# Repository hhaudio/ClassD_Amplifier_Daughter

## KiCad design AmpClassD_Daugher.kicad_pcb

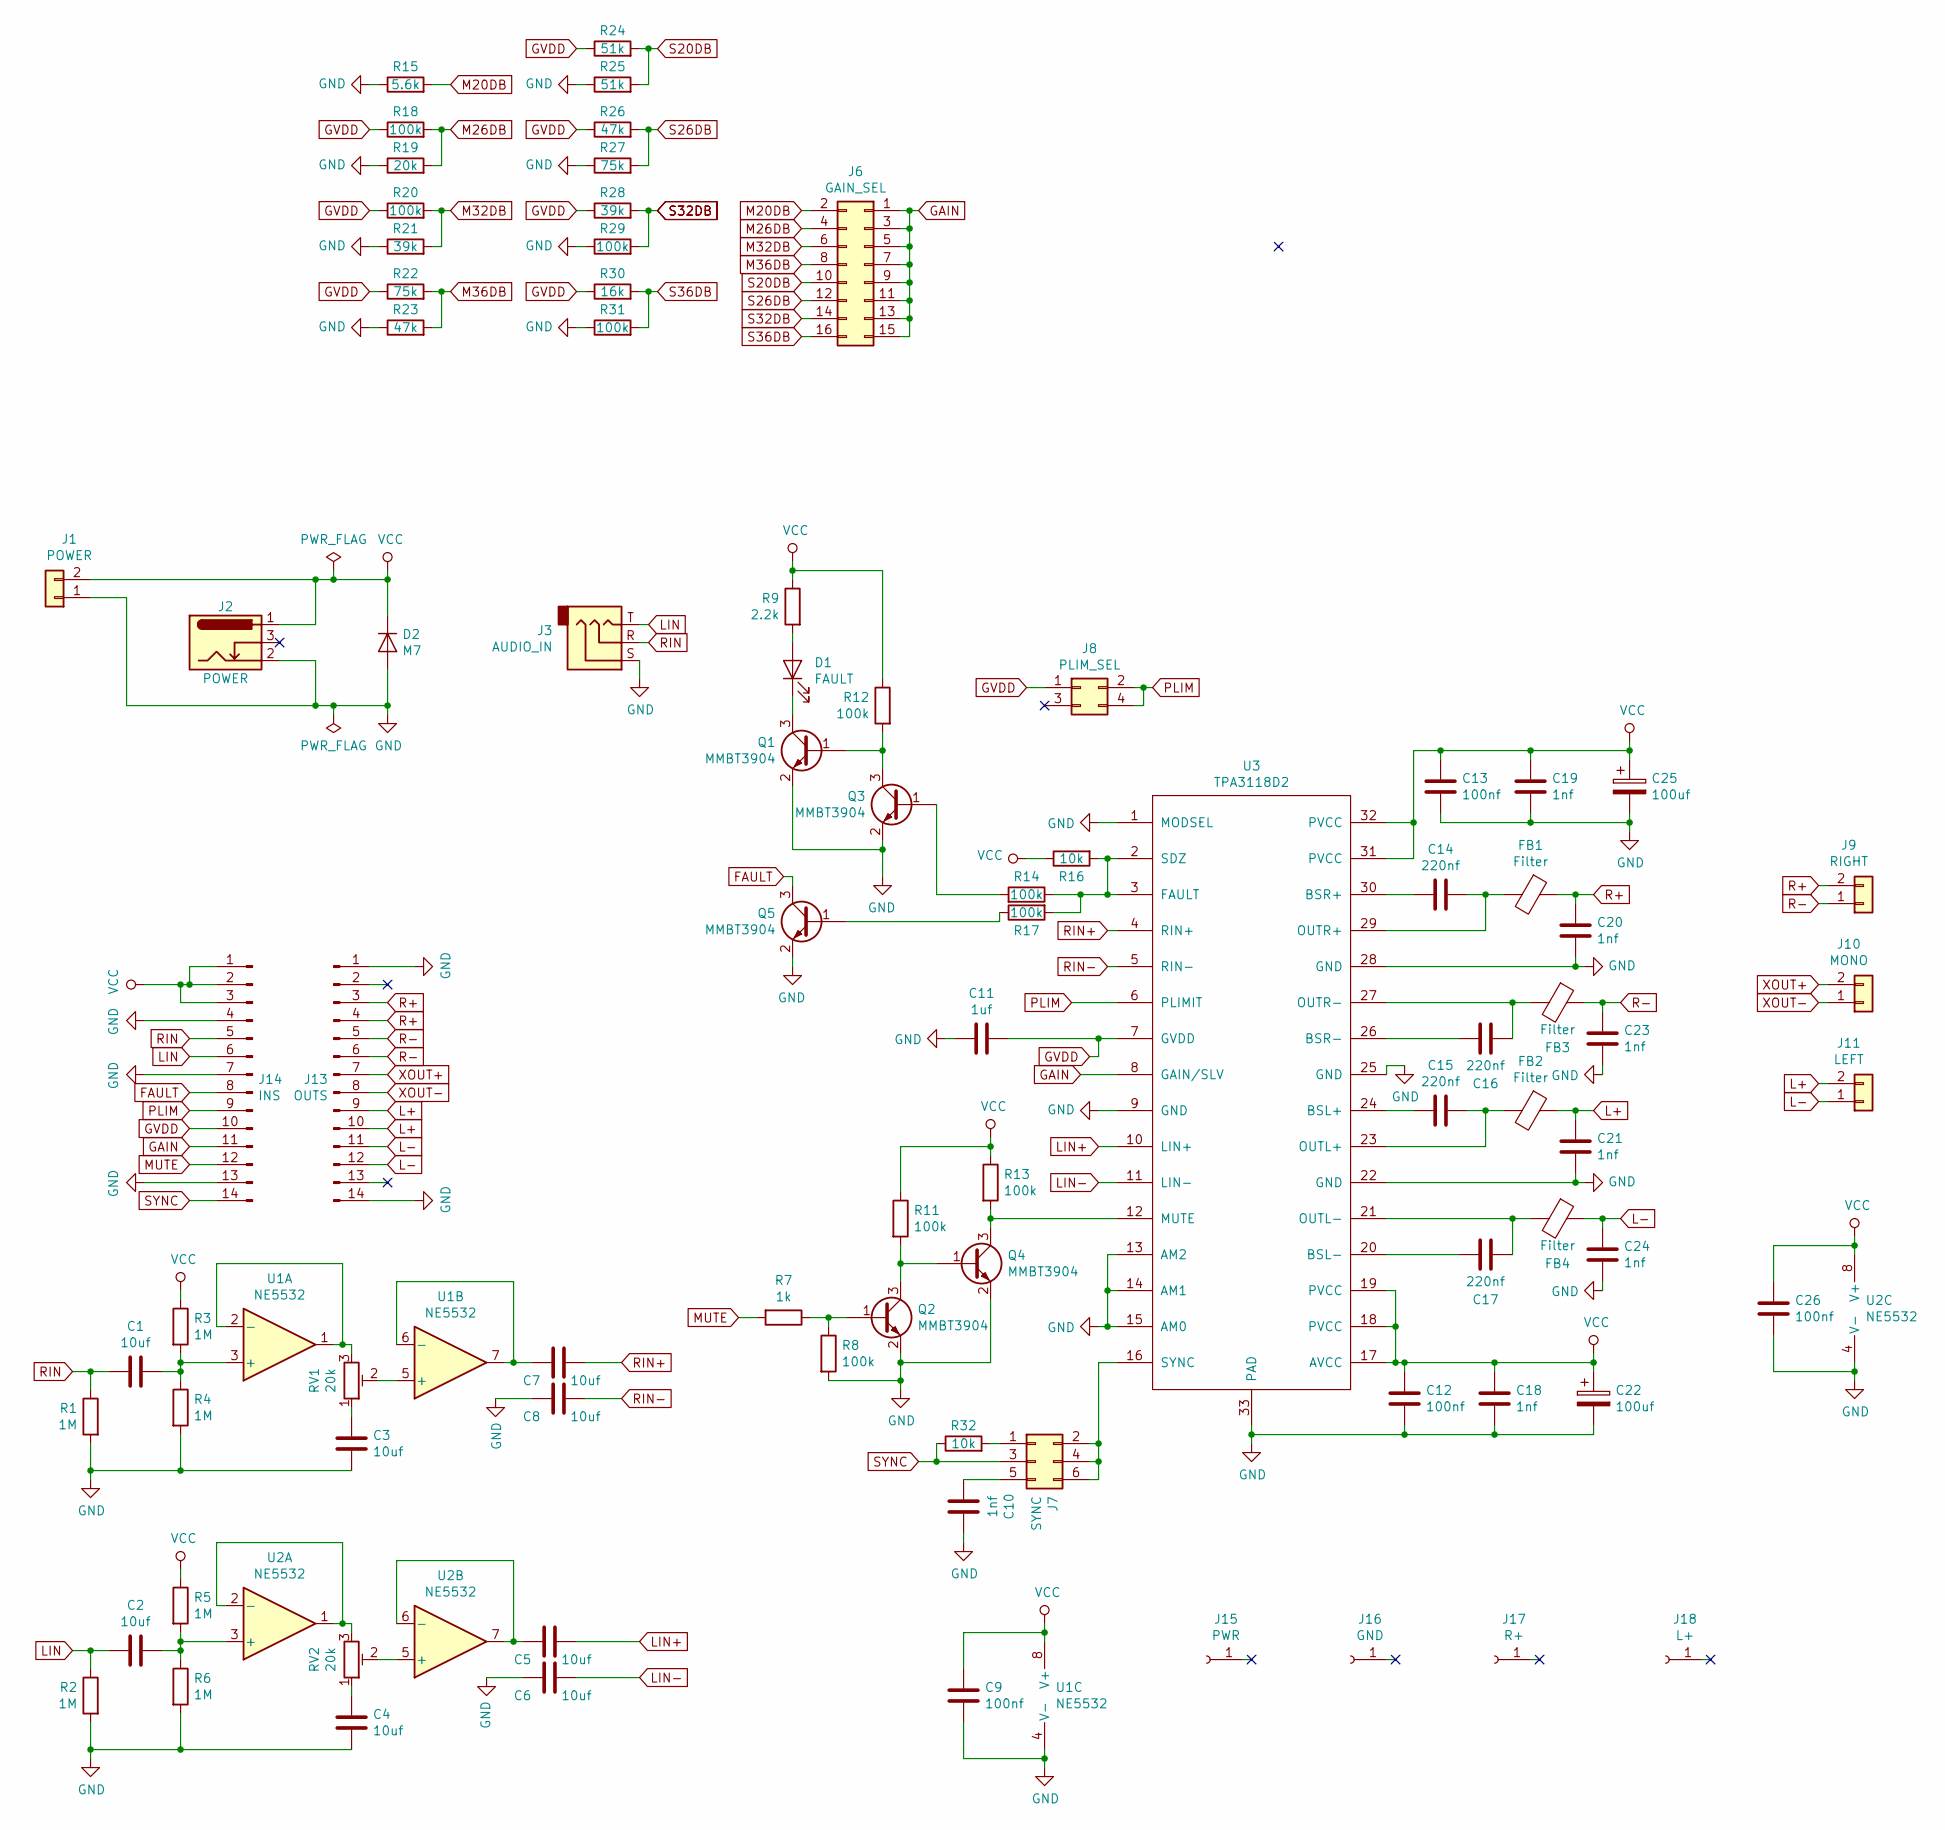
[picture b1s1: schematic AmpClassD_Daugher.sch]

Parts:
C1, C2, C3, C4, C5, C6, C7, C8: 10uf; C_0603_1608Metric_Pad1.05x0.95mm_HandSolder_SmallRef; LCSC C440198
C9, C12, C13, C26: 100nf; C_0603_1608Metric_Pad1.05x0.95mm_HandSolder_SmallRef; LCSC C14663
C10, C18, C19, C20, C21, C23, C24: 1nf; C_0603_1608Metric_Pad1.05x0.95mm_HandSolder_SmallRef; LCSC C1588
C11: 1uf; C_0603_1608Metric_Pad1.05x0.95mm_HandSolder_SmallRef; LCSC C15849
C14, C15, C16, C17: 220nf; C_0603_1608Metric_Pad1.05x0.95mm_HandSolder_SmallRef; LCSC C21120
C22, C25: 100uf; CP_Elec_6.3x7.7; LCSC C311622
D1: FAULT; LED_0805_2012Metric_Pad1.15x1.40mm_HandSolder; LCSC C84256
D2: M7; D_SMA; LCSC C95872
FB1, FB2, FB3, FB4: Filter; L_1206_3216Metric_Pad1.42x1.75mm_HandSolder; LCSC C124704
J1: POWER; Phoenix_Stacked_Marking2_Wider_NoRef_Centered
J2: POWER; SMD_DC_Barrel_JLC; LCSC C397342
J3: AUDIO_IN; 3.5mm_JLC_PJ-321A-4A_TRS_Silk; LCSC C879743
J6: GAIN_SEL; PinHeader_2x08_P2.54mm_Vertical_SMD; LCSC C2884017
J7: SYNC; PinHeader_2x03_P2.54mm_Vertical_SMD; LCSC C780054
J8: PLIM_SEL; PinHeader_2x02_P2.54mm_Vertical_SMD; LCSC C3294460
J9: RIGHT; Phoenix_Stacked_Marking2_Wider_NoRef_Centered
J10: MONO; Phoenix_Stacked_Marking2_Wider_NoRef_Centered
J11: LEFT; Phoenix_Stacked_Marking2_Wider_NoRef_Centered
J13: OUTS; PinHeader_1x14_P2.54mm_Vertical
J14: INS; PinHeader_1x14_P2.54mm_Vertical
J15: PWR; M3_Plated
J16: GND; M3_Plated
J17: R+; M3_Plated
J18: L+; M3_Plated
Q1, Q2, Q3, Q4, Q5: MMBT3904; SOT-23; LCSC C20526
R1, R2, R3, R4, R5, R6: 1M; R_0603_1608Metric_Pad1.05x0.95mm_HandSolder_SmallRef; LCSC C22935
R7: 1k; R_0603_1608Metric_Pad1.05x0.95mm_HandSolder_SmallRef; LCSC C21190
R8, R11, R12, R13, R14, R17, R18, R20, R29, R31: 100k; R_0603_1608Metric_Pad1.05x0.95mm_HandSolder_SmallRef; LCSC C25803
R9: 2.2k; R_0603_1608Metric_Pad1.05x0.95mm_HandSolder_SmallRef; LCSC C4190
R15: 5.6k; R_0603_1608Metric_Pad1.05x0.95mm_HandSolder_SmallRef; LCSC C23189
R16, R32: 10k; R_0603_1608Metric_Pad1.05x0.95mm_HandSolder_SmallRef; LCSC C25804
R19: 20k; R_0603_1608Metric_Pad1.05x0.95mm_HandSolder_SmallRef; LCSC C4184
R21, R28: 39k; R_0603_1608Metric_Pad1.05x0.95mm_HandSolder_SmallRef; LCSC C23153
R22, R27: 75k; R_0603_1608Metric_Pad1.05x0.95mm_HandSolder_SmallRef; LCSC C23242
R23, R26: 47k; R_0603_1608Metric_Pad1.05x0.95mm_HandSolder_SmallRef; LCSC C23162
R24, R25: 51k; R_0603_1608Metric_Pad1.05x0.95mm_HandSolder_SmallRef; LCSC C23196
R30: 16k; R_0603_1608Metric_Pad1.05x0.95mm_HandSolder_SmallRef; LCSC C22818
RV1, RV2: 20k; SMD_TRIM_JLC; LCSC C128550
U1, U2: NE5532; SO-8_3.9x4.9mm_P1.27mm; LCSC C7426
U3: TPA3118D2; HTSSOP-32-1EP_6.1x11mm_P0.65mm_EP5.2x11mm_Mask4.11x4.36mm_T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; LCSC C46497

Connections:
FAULT: J14.8, Q5.3 (C)
GAIN: J6.1, J6.3, J6.5, J6.7, J6.9, J6.11, J6.13, J6.15, J14.11, U3.8 (GAIN/SLV)
GND: C3.2, C4.2, C6.2, C8.2, C9.2, C10.1, C11.2, C12.2, C13.2, C18.2, C19.2, C20.2, C21.2, C22.2, C23.2, C24.2, C25.2, C26.2, D2.2 (A), J1.1, J2.2, J3.S, J13.1, J13.14, J14.4, J14.7, J14.13, Q1.2 (E), Q2.2 (E), Q3.2 (E), Q4.2 (E), Q5.2 (E), R1.2, R2.2, R4.2, R6.2, R8.2, R15.1, R19.1, R21.1, R23.1, R25.1, R27.1, R29.1, R31.1, U1.4 (V-), U2.4 (V-), U3.1 (MODSEL), U3.9 (GND), U3.13 (AM2), U3.14 (AM1), U3.15 (AM0), U3.22 (GND), U3.25 (GND), U3.28 (GND), U3.33 (PAD)
GVDD: C11.1, J8.1, J14.10, R18.1, R20.1, R22.1, R24.1, R26.1, R28.1, R30.1, U3.7 (GVDD)
L+: C21.1, FB2.1, J11.2, J13.9, J13.10
L-: C24.1, FB4.1, J11.1, J13.11, J13.12
LIN: C2.2, J3.T, J14.6, R2.1
LIN+: C5.1, U3.10 (LIN+)
LIN-: C6.1, U3.11 (LIN-)
M20DB: J6.2, R15.2
M26DB: J6.4, R18.2, R19.2
M32DB: J6.6, R20.2, R21.2
M36DB: J6.8, R22.2, R23.2
MUTE: J14.12, R7.2
unnamed: C1.1, R3.2, R4.1, U1.3 (+)
unnamed: C2.1, R5.2, R6.1, U2.3 (+)
unnamed: C3.1, RV1.1
unnamed: C4.1, RV2.1
unnamed: C5.2, U2.6 (-), U2.7
unnamed: C7.2, U1.6 (-), U1.7
unnamed: C10.2, J7.5
unnamed: C14.1, FB1.2, U3.29 (OUTR+)
unnamed: C14.2, U3.30 (BSR+)
unnamed: C15.1, FB2.2, U3.23 (OUTL+)
unnamed: C15.2, U3.24 (BSL+)
unnamed: C16.1, U3.26 (BSR-)
unnamed: C16.2, FB3.2, U3.27 (OUTR-)
unnamed: C17.1, U3.20 (BSL-)
unnamed: C17.2, FB4.2, U3.21 (OUTL-)
unnamed: D1.1 (K), Q1.3 (C)
unnamed: D1.2 (A), R9.2
unnamed: J7.1, R32.2
unnamed: J7.2, J7.4, J7.6, U3.16 (SYNC)
unnamed: Q1.1 (B), Q3.3 (C), R12.2
unnamed: Q2.1 (B), R7.1, R8.1
unnamed: Q2.3 (C), Q4.1 (B), R11.2
unnamed: Q3.1 (B), R14.2
unnamed: Q4.3 (C), R13.2, U3.12 (MUTE)
unnamed: Q5.1 (B), R17.1
unnamed: R14.1, R16.2, R17.2, U3.2 (SDZ), U3.3 (FAULT)
unnamed: RV1.2, U1.5 (+)
unnamed: RV1.3, U1.1, U1.2 (-)
unnamed: RV2.2, U2.5 (+)
unnamed: RV2.3, U2.1, U2.2 (-)
PLIM: J8.2, J8.4, J14.9, U3.6 (PLIMIT)
R+: C20.1, FB1.1, J9.2, J13.3, J13.4
R-: C23.1, FB3.1, J9.1, J13.5, J13.6
RIN: C1.2, J3.R, J14.5, R1.1
RIN+: C7.1, U3.4 (RIN+)
RIN-: C8.1, U3.5 (RIN-)
S20DB: J6.10, R24.2, R25.2
S26DB: J6.12, R26.2, R27.2
S32DB: J6.14, R28.2, R29.2
S36DB: J6.16, R30.2, R31.2
SYNC: J7.3, J14.14, R32.1
VCC: C9.1, C12.1, C13.1, C18.1, C19.1, C22.1, C25.1, C26.1, D2.1 (K), J1.2, J2.1, J14.1, J14.2, J14.3, R3.1, R5.1, R9.1, R11.1, R12.1, R13.1, R16.1, U1.8 (V+), U2.8 (V+), U3.17 (AVCC), U3.18 (PVCC), U3.19 (PVCC), U3.31 (PVCC), U3.32 (PVCC)
XOUT+: J10.2, J13.7
XOUT-: J10.1, J13.8

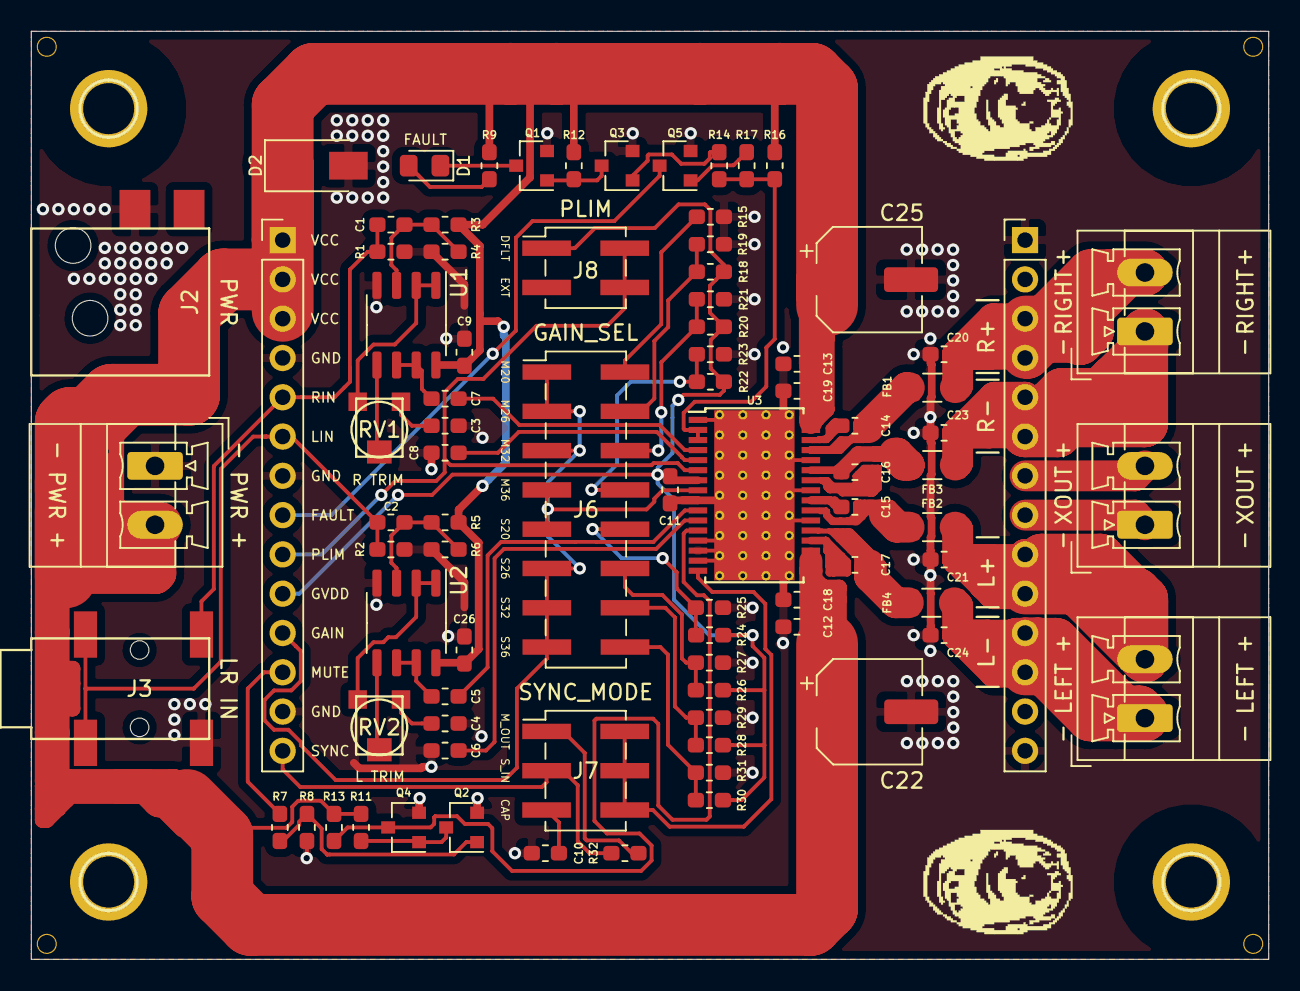
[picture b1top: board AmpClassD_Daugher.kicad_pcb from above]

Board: 2 copper layers, 80.0 x 60.0 mm, 88 parts (0 on the bottom side), 58 nets.

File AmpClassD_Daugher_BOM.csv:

Comment,Designator,Footprint,LCSC
"1uf","C11","Capacitor_SMD:C_0603_1608Metric_Pad1.05x0.95mm_HandSolder_SmallRef","C15849"
"100nf","C9,C12,C13,C26","Capacitor_SMD:C_0603_1608Metric_Pad1.05x0.95mm_HandSolder_SmallRef","C14663"
"220nf","C14,C15,C16,C17","Capacitor_SMD:C_0603_1608Metric_Pad1.05x0.95mm_HandSolder_SmallRef","C21120"
"1nf","C10,C18,C19,C20,C21,C23,C24","Capacitor_SMD:C_0603_1608Metric_Pad1.05x0.95mm_HandSolder_SmallRef","C1588"
"100uf","C22,C25","Capacitor_SMD:CP_Elec_6.3x7.7","C311622"
"10uf","C1,C2,C3,C4,C5,C6,C7,C8","Capacitor_SMD:C_0603_1608Metric_Pad1.05x0.95mm_HandSolder_SmallRef","C440198"
"FAULT","D1","LED_SMD:LED_0805_2012Metric_Pad1.15x1.40mm_HandSolder","C84256"
"M7","D2","Diode_SMD:D_SMA","C95872"
"Filter","FB1,FB2,FB3,FB4","Inductor_SMD:L_1206_3216Metric_Pad1.42x1.75mm_HandSolder","C124704"
"POWER","J1","HammerheadAudio:Phoenix_Stacked_Marking2_Wider_NoRef_Centered",""
"MONO","J10","HammerheadAudio:Phoenix_Stacked_Marking2_Wider_NoRef_Centered",""
"LEFT","J11","HammerheadAudio:Phoenix_Stacked_Marking2_Wider_NoRef_Centered",""
"OUTS","J13","Connector_PinHeader_2.54mm:PinHeader_1x14_P2.54mm_Vertical",""
"INS","J14","Connector_PinHeader_2.54mm:PinHeader_1x14_P2.54mm_Vertical",""
"PWR","J15","HammerheadAudio:M3_Plated",""
"GND","J16","HammerheadAudio:M3_Plated",""
"R+","J17","HammerheadAudio:M3_Plated",""
"L+","J18","HammerheadAudio:M3_Plated",""
"POWER","J2","Crossley_Footprints:SMD_DC_Barrel_JLC","C397342"
"AUDIO_IN","J3","HammerheadAudio:3.5mm_JLC_PJ-321A-4A_TRS_Silk","C879743"
"GAIN_SEL","J6","Connector_PinHeader_2.54mm:PinHeader_2x08_P2.54mm_Vertical_SMD","C2884017"
"SYNC","J7","Connector_PinHeader_2.54mm:PinHeader_2x03_P2.54mm_Vertical_SMD","C780054"
"PLIM_SEL","J8","Connector_PinHeader_2.54mm:PinHeader_2x02_P2.54mm_Vertical_SMD","C3294460"
"RIGHT","J9","HammerheadAudio:Phoenix_Stacked_Marking2_Wider_NoRef_Centered",""
"MMBT3904","Q1,Q2,Q3,Q4,Q5","Package_TO_SOT_SMD:SOT-23","C20526"
"100k","R8,R11,R12,R13,R14,R17,R18,R20,R29,R31","Resistor_SMD:R_0603_1608Metric_Pad1.05x0.95mm_HandSolder_SmallRef","C25803"
"5.6k","R15","Resistor_SMD:R_0603_1608Metric_Pad1.05x0.95mm_HandSolder_SmallRef","C23189"
"10k","R16,R32","Resistor_SMD:R_0603_1608Metric_Pad1.05x0.95mm_HandSolder_SmallRef","C25804"
"20k","R19","Resistor_SMD:R_0603_1608Metric_Pad1.05x0.95mm_HandSolder_SmallRef","C4184"
"39k","R21,R28","Resistor_SMD:R_0603_1608Metric_Pad1.05x0.95mm_HandSolder_SmallRef","C23153"
"75k","R22,R27","Resistor_SMD:R_0603_1608Metric_Pad1.05x0.95mm_HandSolder_SmallRef","C23242"
"47k","R23,R26","Resistor_SMD:R_0603_1608Metric_Pad1.05x0.95mm_HandSolder_SmallRef","C23162"
"51k","R24,R25","Resistor_SMD:R_0603_1608Metric_Pad1.05x0.95mm_HandSolder_SmallRef","C23196"
"1M","R1,R2,R3,R4,R5,R6","Resistor_SMD:R_0603_1608Metric_Pad1.05x0.95mm_HandSolder_SmallRef","C22935"
"16k","R30","Resistor_SMD:R_0603_1608Metric_Pad1.05x0.95mm_HandSolder_SmallRef","C22818"
"1k","R7","Resistor_SMD:R_0603_1608Metric_Pad1.05x0.95mm_HandSolder_SmallRef","C21190"
"2.2k","R9","Resistor_SMD:R_0603_1608Metric_Pad1.05x0.95mm_HandSolder_SmallRef","C4190"
"20k","RV1,RV2","Crossley_Footprints:SMD_TRIM_JLC","C128550"
"NE5532","U1,U2","Package_SO:SO-8_3.9x4.9mm_P1.27mm","C7426"
"TPA3118D2","U3","Package_SO:HTSSOP-32-1EP_6.1x11mm_P0.65mm_EP5.2x11mm_Mask4.11x4.36mm_ThermalVias","C46497"

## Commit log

2022-02-13 fixed preamp circuit
2022-02-13 schematic updates
2022-02-13 layout progress
2022-02-14 initial layout finished
2023-07-04 updated schematic
2023-07-05 schematic
2023-07-06 update finished
